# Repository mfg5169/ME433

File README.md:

Instead of having the HWs spread out like before, I've recompiled them all into 1 big repo, making it easier to follow

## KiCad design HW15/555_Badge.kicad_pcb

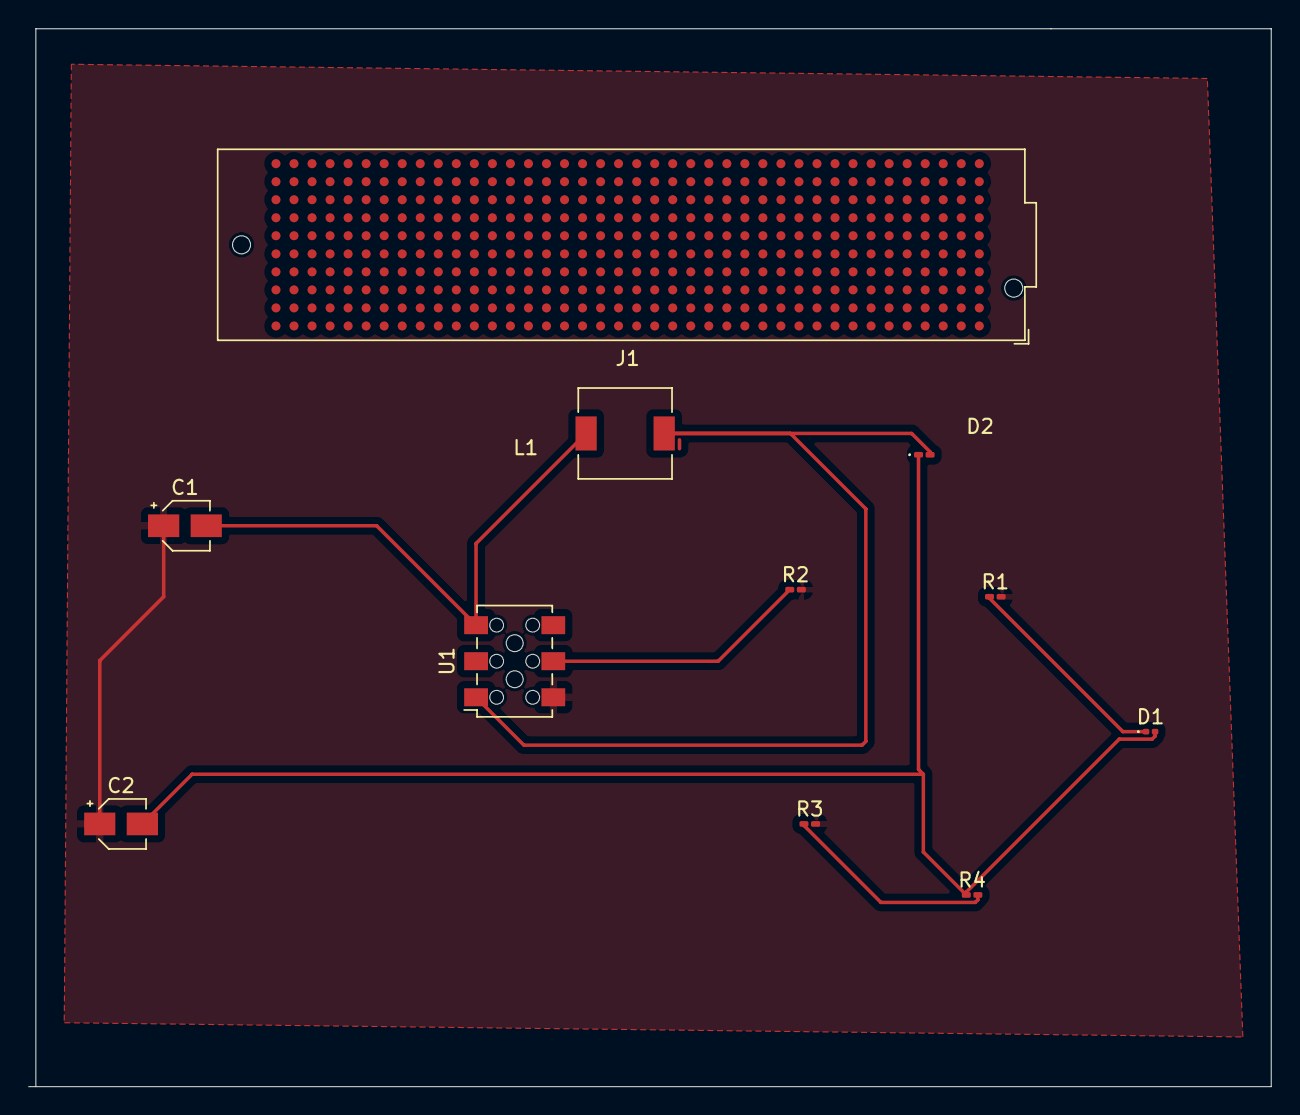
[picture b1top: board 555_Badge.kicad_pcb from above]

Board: 2 copper layers, 87.5 x 74.5 mm, 11 parts (0 on the bottom side), 7 nets.

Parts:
C1, C2: 22uF; CP_Elec_3x5.3
D1: RED; D_0201_0603Metric
D2: D_Schottky; D_0201_0603Metric_Pad0.64x0.40mm_HandSolder
J1: Conn_01x03_Pin; Samtec_FMC_ASP-134486-01_10x40_P1.27mm_Vertical
L1: L; L_6.3x6.3_H3
R1: 1k; R_0201_0603Metric_Pad0.64x0.40mm_HandSolder
R2: 20k; R_0201_0603Metric_Pad0.64x0.40mm_HandSolder
R3: 215k; R_0201_0603Metric_Pad0.64x0.40mm_HandSolder
R4: 110k; R_0201_0603Metric_Pad0.64x0.40mm_HandSolder
U1: Samtec_HLE-103-02-xxx-DV-BE-LC_2x03_P2.54mm_Horizontal

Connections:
+5V: C2.2, D1.2 (A), D2.1 (K), R4.1
GND: C1.1, C2.1, R1.2, R2.2, R3.2, U1.2 (2-GND)
unnamed: D1.1 (K), R1.1
unnamed: D2.2 (A), L1.2, U1.1 (1-SW)
unnamed: R3.1, R4.2, U1.3 (3-FB)
unnamed: R2.1, U1.4 (4-OC)
VCC: C1.2, L1.1, U1.5 (5-VIN), U1.6 (6-EN)

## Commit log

2025-06-05 renamed hw3
2025-06-05 renamed hw4
2025-06-05 photos
2025-06-05 image
2025-06-05 homework 9 and 10
2025-06-05 testing push
2025-06-05 remove empty folder
2025-06-05 error update
2025-06-05 HW11
2025-06-05 HW15
2025-06-05 HW16
2025-06-05 HW12 and HW13
